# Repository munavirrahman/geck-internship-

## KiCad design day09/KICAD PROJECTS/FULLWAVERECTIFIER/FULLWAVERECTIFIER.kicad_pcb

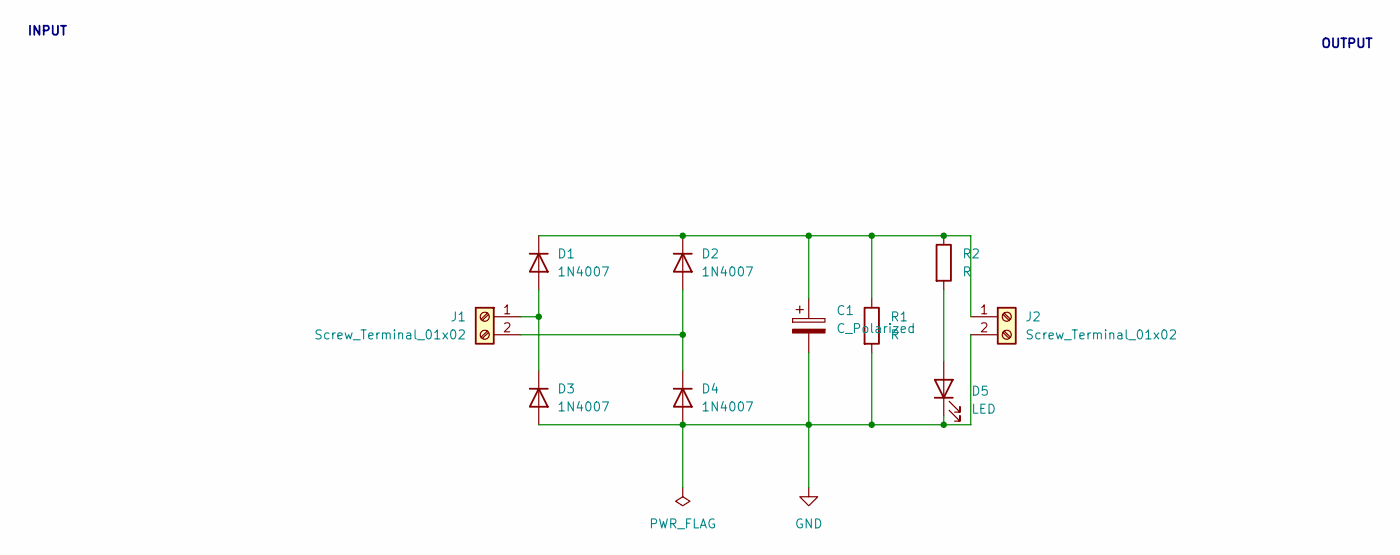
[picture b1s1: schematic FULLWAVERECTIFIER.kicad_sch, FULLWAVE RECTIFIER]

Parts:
C1: C_Polarized; CP_Radial_D10.0mm_P2.50mm_P5.00mm
D1, D2, D3, D4: 1N4007; D_DO-41_SOD81_P10.16mm_Horizontal
D5: LED; LED_D5.0mm_Horizontal_O3.81mm_Z3.0mm
J1, J2: Screw_Terminal_01x02; TerminalBlock_MaiXu_MX126-5.0-02P_1x02_P5.00mm
R1, R2: R; R_Axial_DIN0204_L3.6mm_D1.6mm_P5.08mm_Horizontal

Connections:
GND: C1.2, D3.2 (A), D4.2 (A), D5.1 (K), J2.2, R1.2
unnamed: D1.2 (A), D3.1 (K), J1.1
unnamed: C1.1, D1.1 (K), D2.1 (K), J2.1, R1.1, R2.1
unnamed: D2.2 (A), D4.1 (K), J1.2
unnamed: D5.2 (A), R2.2

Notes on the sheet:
OUTPUT
INPUT

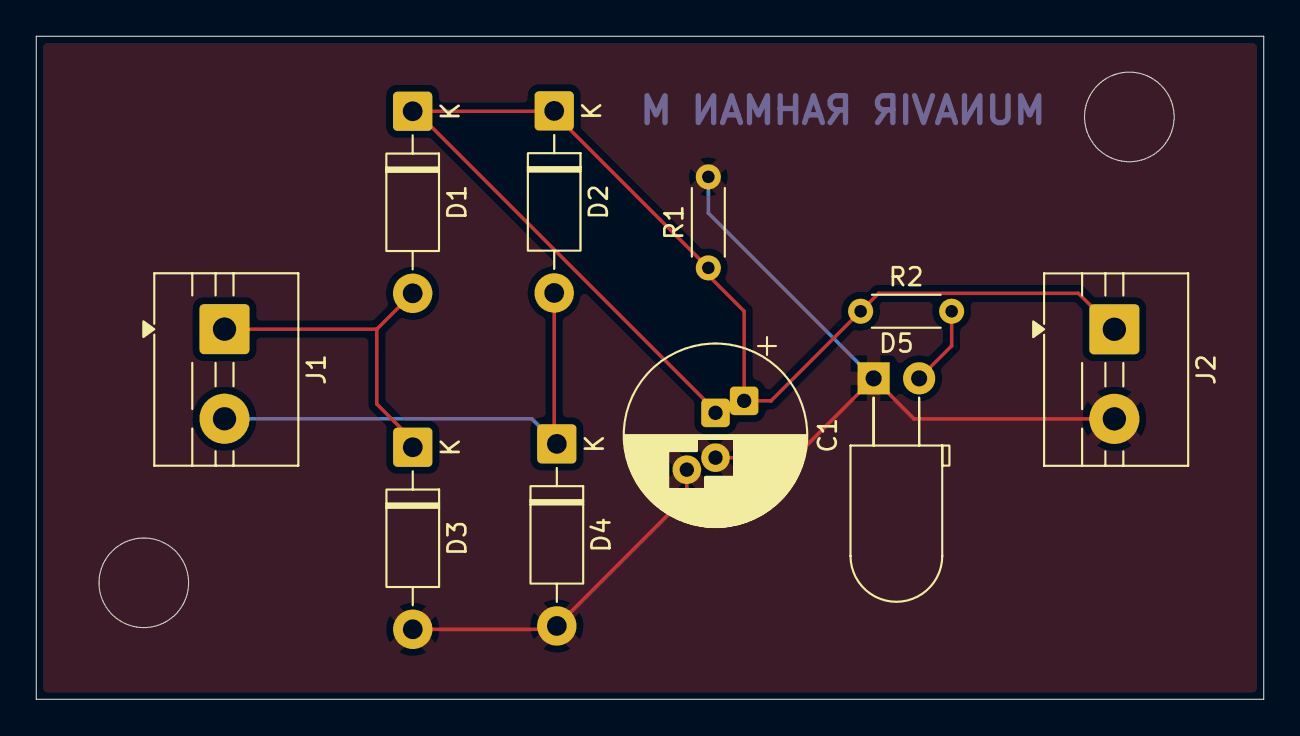
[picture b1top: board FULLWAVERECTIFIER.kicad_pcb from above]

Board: 2 copper layers, 68.5 x 37.0 mm, 10 parts (0 on the bottom side), 5 nets.

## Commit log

2026-06-18 Add README
2026-06-18 my task was completed
2026-06-18 doc: add task completed
2026-06-18 success
2026-06-19 Day 2 - updated project UI and features
2026-06-24 ESP32_WEBSERVER
2026-06-25 day8,day7
2026-06-27 PCB DESIGN
